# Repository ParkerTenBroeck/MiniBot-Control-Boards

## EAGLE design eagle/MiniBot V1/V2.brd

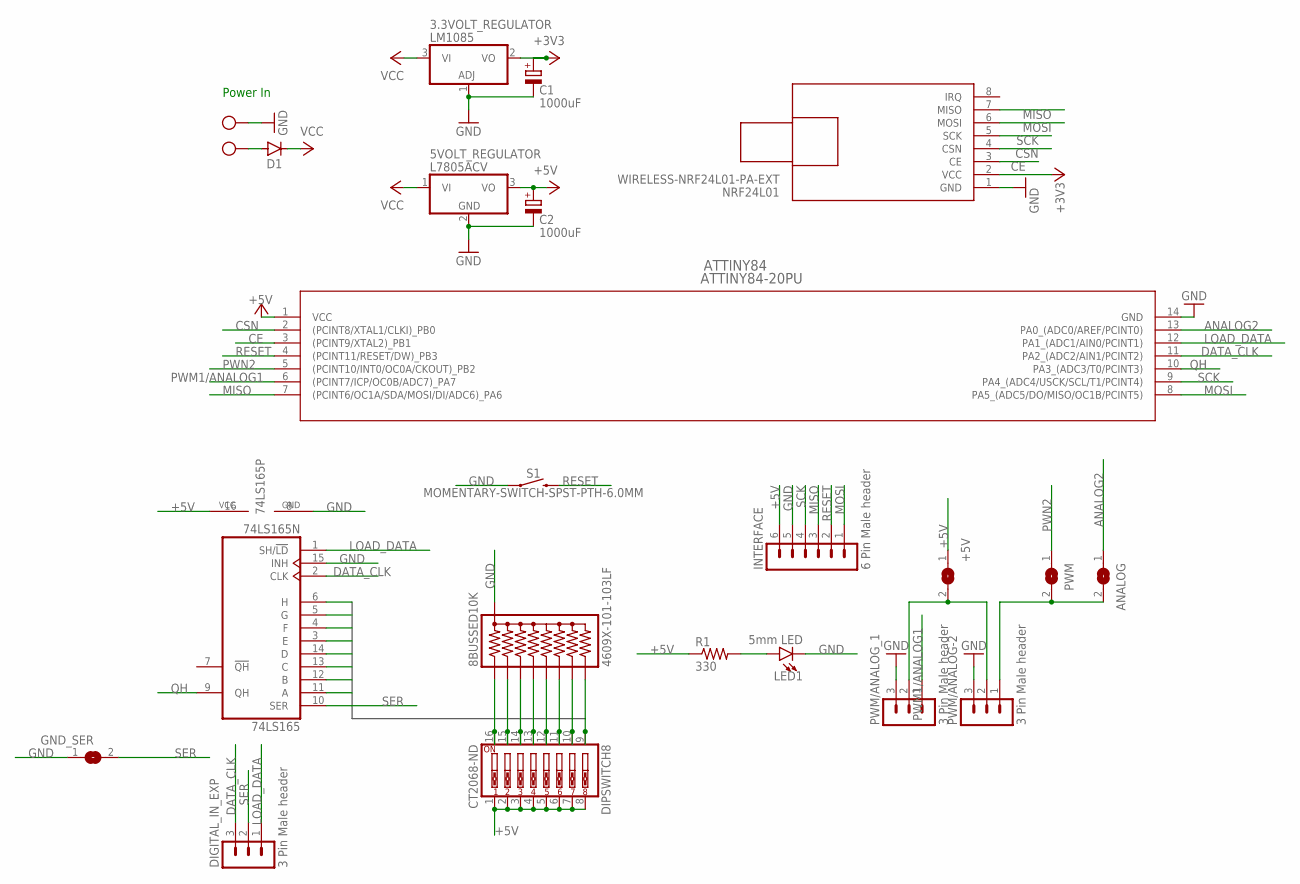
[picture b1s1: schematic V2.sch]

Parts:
3.3VOLT_REGULATOR: LM1085; TO220V
5VOLT_REGULATOR: L7805ACV; TO220V
8BUSSED10K: 4609X-101-103LF; RPACK-SIP-PTH-8
74LS165: 74LS165N; DIL16
+5V: SJW
ANALOG: SJW
ATTINY84: ATTINY84-20PU; 14P3
C1, C2: 1000uF; E2,5-6
D1: 1N5060GP; DO15-12
DIGITAL_IN_EXP: 3 Pin Male header; MA03-1
DIPSWITCH8: CT2068-ND; EDG-08
GND_SER: SJW
INTERFACE: 6 Pin Male header; MA06-1
LED1: 5mm LED; LED_5MM
NRF24L01: WIRELESS-NRF24L01-PA-EXT
PWM: SJW
PWM/ANALOG-2: 3 Pin Male header; MA03-1
PWM/ANALOG_1: 3 Pin Male header; MA03-1
R1: 330; 0204/7
S1: MOMENTARY-SWITCH-SPST-PTH-6.0MM; TACTILE_SWITCH_PTH_6.0MM
X1: MKDSN1,5/2-5,08

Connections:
+3V3: 3.3VOLT_REGULATOR.2 (VO), C1.+, NRF24L01.2 (VCC)
+5V: 5VOLT_REGULATOR.3 (VO), 74LS165.16 (VCC), +5V.1, ATTINY84.1 (VCC), C2.+, DIPSWITCH8.1, DIPSWITCH8.2, DIPSWITCH8.3, DIPSWITCH8.4, DIPSWITCH8.5, DIPSWITCH8.6, DIPSWITCH8.7, DIPSWITCH8.8, INTERFACE.6, R1.1
ANALOG2: ANALOG.1, ATTINY84.13 (PA0_(ADC0/AREF/PCINT0))
BIT0: 8BUSSED10K.P$2 (2), 74LS165.11 (A), DIPSWITCH8.16
BIT1: 8BUSSED10K.P$3 (3), 74LS165.12 (B), DIPSWITCH8.15
BIT2: 8BUSSED10K.P$4 (4), 74LS165.13 (C), DIPSWITCH8.14
BIT3: 8BUSSED10K.P$5 (5), 74LS165.14 (D), DIPSWITCH8.13
BIT4: 8BUSSED10K.P$6 (6), 74LS165.3 (E), DIPSWITCH8.12
BIT5: 8BUSSED10K.P$7 (7), 74LS165.4 (F), DIPSWITCH8.11
BIT6: 8BUSSED10K.P$8 (8), 74LS165.5 (G), DIPSWITCH8.10
BIT7: 8BUSSED10K.P$9 (9), 74LS165.6 (H), DIPSWITCH8.9
CE: ATTINY84.3 ((PCINT9/XTAL2)_PB1), NRF24L01.3 (CE)
CSN: ATTINY84.2 ((PCINT8/XTAL1/CLKI)_PB0), NRF24L01.4 (CSN)
DATA_CLK: 74LS165.2 (CLK), ATTINY84.11 (PA2_(ADC2/AIN1/PCINT2)), DIGITAL_IN_EXP.3
GND: 3.3VOLT_REGULATOR.1 (ADJ), 5VOLT_REGULATOR.2 (GND), 8BUSSED10K.P$1 (1), 74LS165.8 (GND), 74LS165.15 (INH), ATTINY84.14 (GND), C1.-, C2.-, GND_SER.1, INTERFACE.5, LED1.K (C), NRF24L01.1 (GND), PWM/ANALOG-2.3, PWM/ANALOG_1.3, S1.1, X1.2
LOAD_DATA: 74LS165.1 (SH/!LD), ATTINY84.12 (PA1_(ADC1/AIN0/PCINT1)), DIGITAL_IN_EXP.1
MISO: ATTINY84.7 ((PCINT6/OC1A/SDA/MOSI/DI/ADC6)_PA6), INTERFACE.3, NRF24L01.7 (MISO)
MOSI: ATTINY84.8 (PA5_(ADC5/DO/MISO/OC1B/PCINT5)), INTERFACE.1, NRF24L01.6 (MOSI)
unnamed: +5V.2, PWM/ANALOG-2.2, PWM/ANALOG_1.2
unnamed: ANALOG.2, PWM.2, PWM/ANALOG-2.1
unnamed: LED1.A, R1.2
unnamed: D1.A, X1.1
PWM1/ANALOG1: ATTINY84.6 ((PCINT7/ICP/OC0B/ADC7)_PA7), PWM/ANALOG_1.1
PWN2: ATTINY84.5 ((PCINT10/INT0/OC0A/CKOUT)_PB2), PWM.1
QH: 74LS165.9 (QH), ATTINY84.10 (PA3_(ADC3/T0/PCINT3))
RESET: ATTINY84.4 ((PCINT11/RESET/DW)_PB3), INTERFACE.2, S1.3 (2)
SCK: ATTINY84.9 (PA4_(ADC4/USCK/SCL/T1/PCINT4)), INTERFACE.4, NRF24L01.5 (SCK)
SER: 74LS165.10 (SER), DIGITAL_IN_EXP.2, GND_SER.2
VCC: 3.3VOLT_REGULATOR.3 (VI), 5VOLT_REGULATOR.1 (VI), D1.C

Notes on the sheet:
Power In

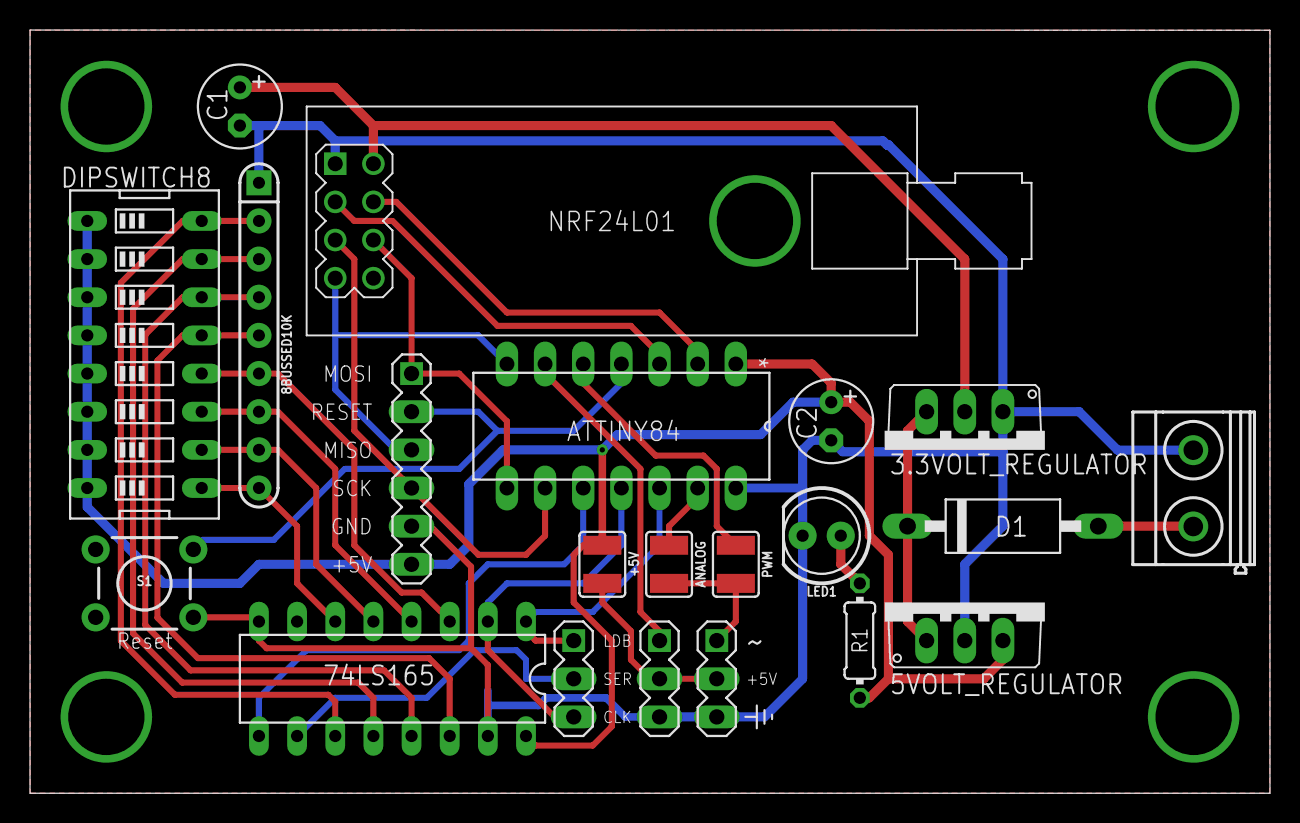
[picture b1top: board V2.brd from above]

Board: 2 copper layers, 82.5 x 50.8 mm, 22 parts (1 on the bottom side), 29 nets.

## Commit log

2021-08-05 added content

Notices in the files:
parts and their libraries:
NEF24L01-Full: Released under the Creative Commons Attribution 4.0 International License: http://creativecommons.org/licenses/by/4.0
SparkFun-Resistors: Licensing: Creative Commons ShareAlike 4.0 International - https://creativecommons.org/licenses/by-sa/4.0
